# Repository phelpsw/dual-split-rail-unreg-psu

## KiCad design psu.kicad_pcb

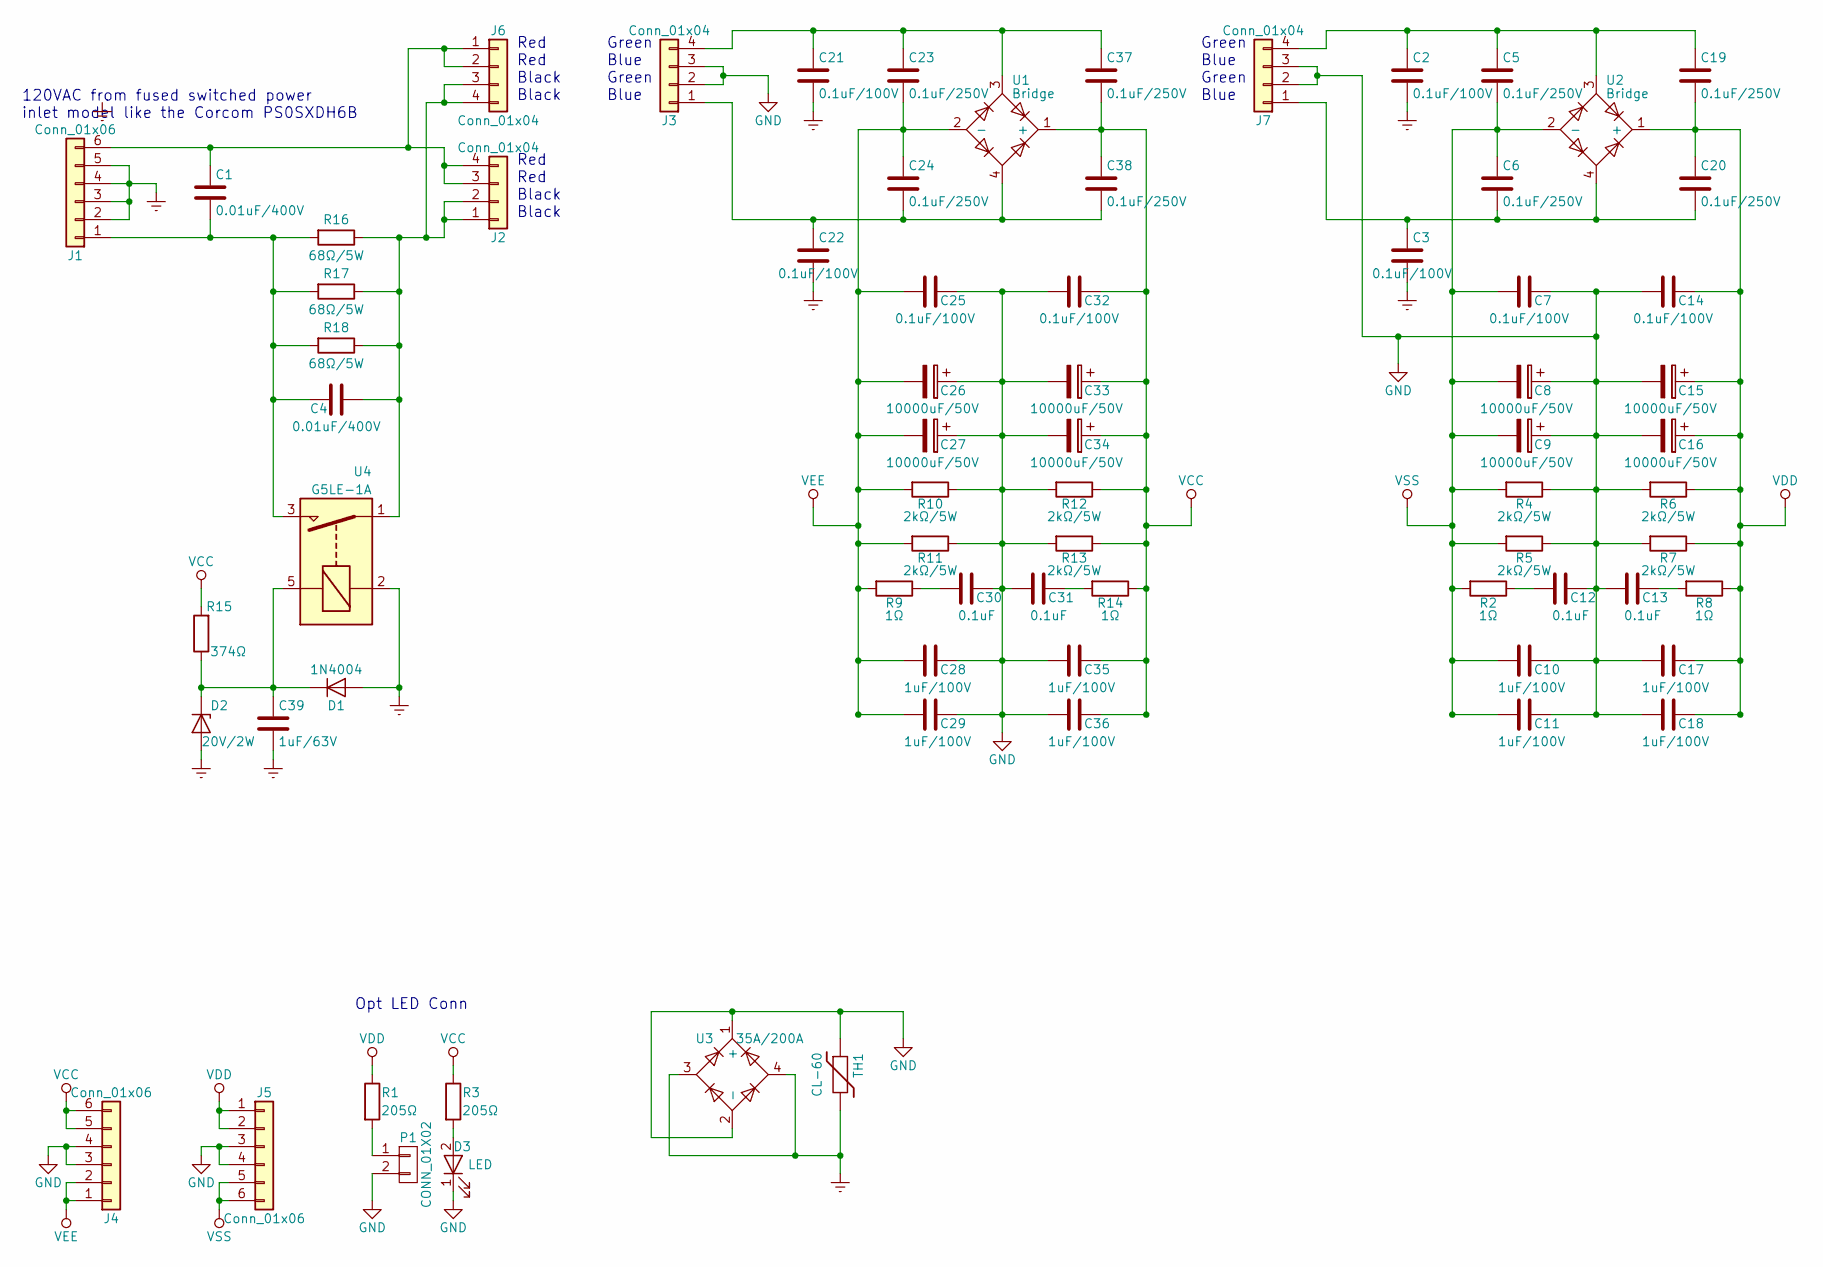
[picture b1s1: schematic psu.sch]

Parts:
C1, C4: 0.01uF/400V; C_Rect_L13.0mm_W4.0mm_P10.00mm_FKS3_FKP3_MKS4
C2, C3, C7, C14, C21, C22, C25, C32: 0.1uF/100V; C_Rect_L7.0mm_W3.5mm_P5.00mm
C5, C6, C19, C20, C23, C24, C37, C38: 0.1uF/250V; C_Rect_L10.3mm_W7.2mm_P7.50mm_MKS4
C8, C9, C15, C16, C26, C27, C33, C34: 10000uF/50V; CP_Radial_D35.0mm_P10.00mm_SnapIn
C10, C11, C17, C18, C28, C29, C35, C36: 1uF/100V; C_Rect_L13.0mm_W6.0mm_P10.00mm_FKS3_FKP3_MKS4
C12, C13, C30, C31: 0.1uF; C_Rect_L7.0mm_W3.5mm_P5.00mm
C39: 1uF/63V; CP_Radial_D5.0mm_P2.00mm
D1: 1N4004; D_DO-41_SOD81_P10.16mm_Horizontal
D2: 20V/2W; D_DO-41_SOD81_P10.16mm_Horizontal
D3: LED; LED_D5.0mm
J1, J4, J5: Conn_01x06; Phoenix-MKDS-6
J2, J3, J6, J7: Conn_01x04; Phoenix-MKDS-4
P1: CONN_01X02; JST_XH_B02B-XH-A_02x2.50mm_Straight
R1, R3: 205Ω; R_Axial_DIN0207_L6.3mm_D2.5mm_P10.16mm_Horizontal
R2, R8, R9, R14: 1Ω; R_Axial_DIN0207_L6.3mm_D2.5mm_P10.16mm_Horizontal
R4, R5, R6, R7, R10, R11, R12, R13: 2kΩ/5W; R_Axial_Power_L25.0mm_W9.0mm_P30.48mm
R15: 374Ω; R_Axial_DIN0309_L9.0mm_D3.2mm_P15.24mm_Horizontal
R16, R17, R18: 68Ω/5W; R_Axial_Power_L25.0mm_W9.0mm_P30.48mm
TH1: CL-60; RV_Disc_D21.5_W5.8_P10
U1, U2: Bridge; GBPC-W
U3: 35A/200A; Diode_Bridge_18.5x5.5
U4: G5LE-1A; Relay_Omron_G5LE-1A4

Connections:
Earth: C2.2, C3.2, C21.2, C22.2, C39.2, D1.2 (A), D2.2 (A), J1.2, J1.3, J1.4, J1.5, TH1.2, U3.3, U3.4, U4.2
GND: C7.1, C8.1, C9.1, C10.1, C11.1, C12.1, C13.2, C14.2, C15.2, C16.2, C17.2, C18.2, C25.1, C26.1, C27.1, C28.1, C29.1, C30.1, C31.2, C32.2, C33.2, C34.2, C35.2, C36.2, D3.1 (K), J3.2, J3.3, J4.3, J4.4, J5.3, J5.4, J7.2, J7.3, P1.2, R4.1, R5.1, R6.2, R7.2, R10.1, R11.1, R12.2, R13.2, TH1.1, U3.1 (+), U3.2 (-)
unnamed: C1.1, J1.6, J2.3, J2.4, J6.1, J6.2
unnamed: C1.2, C4.2, J1.1, R16.2, R17.2, R18.2, U4.3
unnamed: C4.1, J2.1, J2.2, J6.3, J6.4, R16.1, R17.1, R18.1, U4.1
unnamed: C12.2, R2.1
unnamed: C13.1, R8.2
unnamed: C2.1, C5.1, C19.1, J7.4, U2.3
unnamed: C3.1, C6.2, C20.2, J7.1, U2.4
unnamed: C21.1, C23.1, C37.1, J3.4, U1.3
unnamed: C22.1, C24.2, C38.2, J3.1, U1.4
unnamed: C30.2, R9.1
unnamed: C31.1, R14.2
unnamed: C39.1, D1.1 (K), D2.1 (K), R15.1, U4.5
unnamed: D3.2 (A), R3.2
unnamed: P1.1, R1.2
VCC: C32.1, C33.1, C34.1, C35.1, C36.1, C37.2, C38.1, J4.5, J4.6, R3.1, R12.1, R13.1, R14.1, R15.2, U1.1 (+)
VDD: C14.1, C15.1, C16.1, C17.1, C18.1, C19.2, C20.1, J5.1, J5.2, R1.1, R6.1, R7.1, R8.1, U2.1 (+)
VEE: C23.2, C24.1, C25.2, C26.2, C27.2, C28.2, C29.2, J4.1, J4.2, R9.2, R10.2, R11.2, U1.2 (-)
VSS: C5.2, C6.1, C7.2, C8.2, C9.2, C10.2, C11.2, J5.5, J5.6, R2.2, R4.2, R5.2, U2.2 (-)

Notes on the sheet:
Red Red Black Black
Green Blue Green Blue
Opt LED Conn
120VAC from fused switched power inlet model like the Corcom PS0SXDH6B

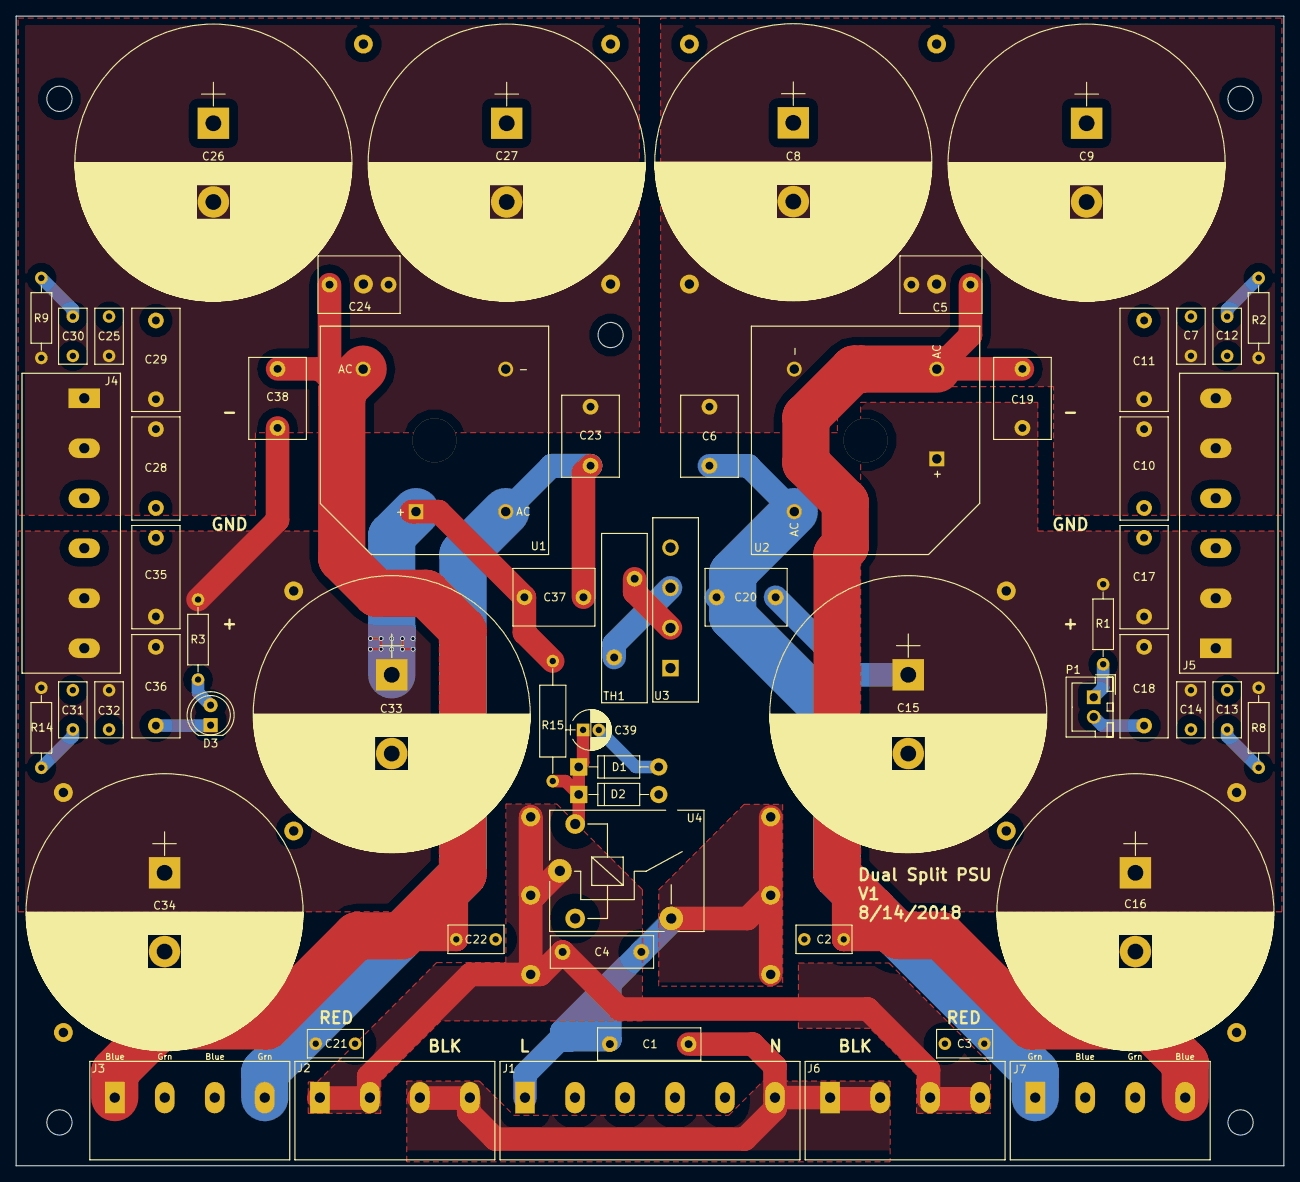
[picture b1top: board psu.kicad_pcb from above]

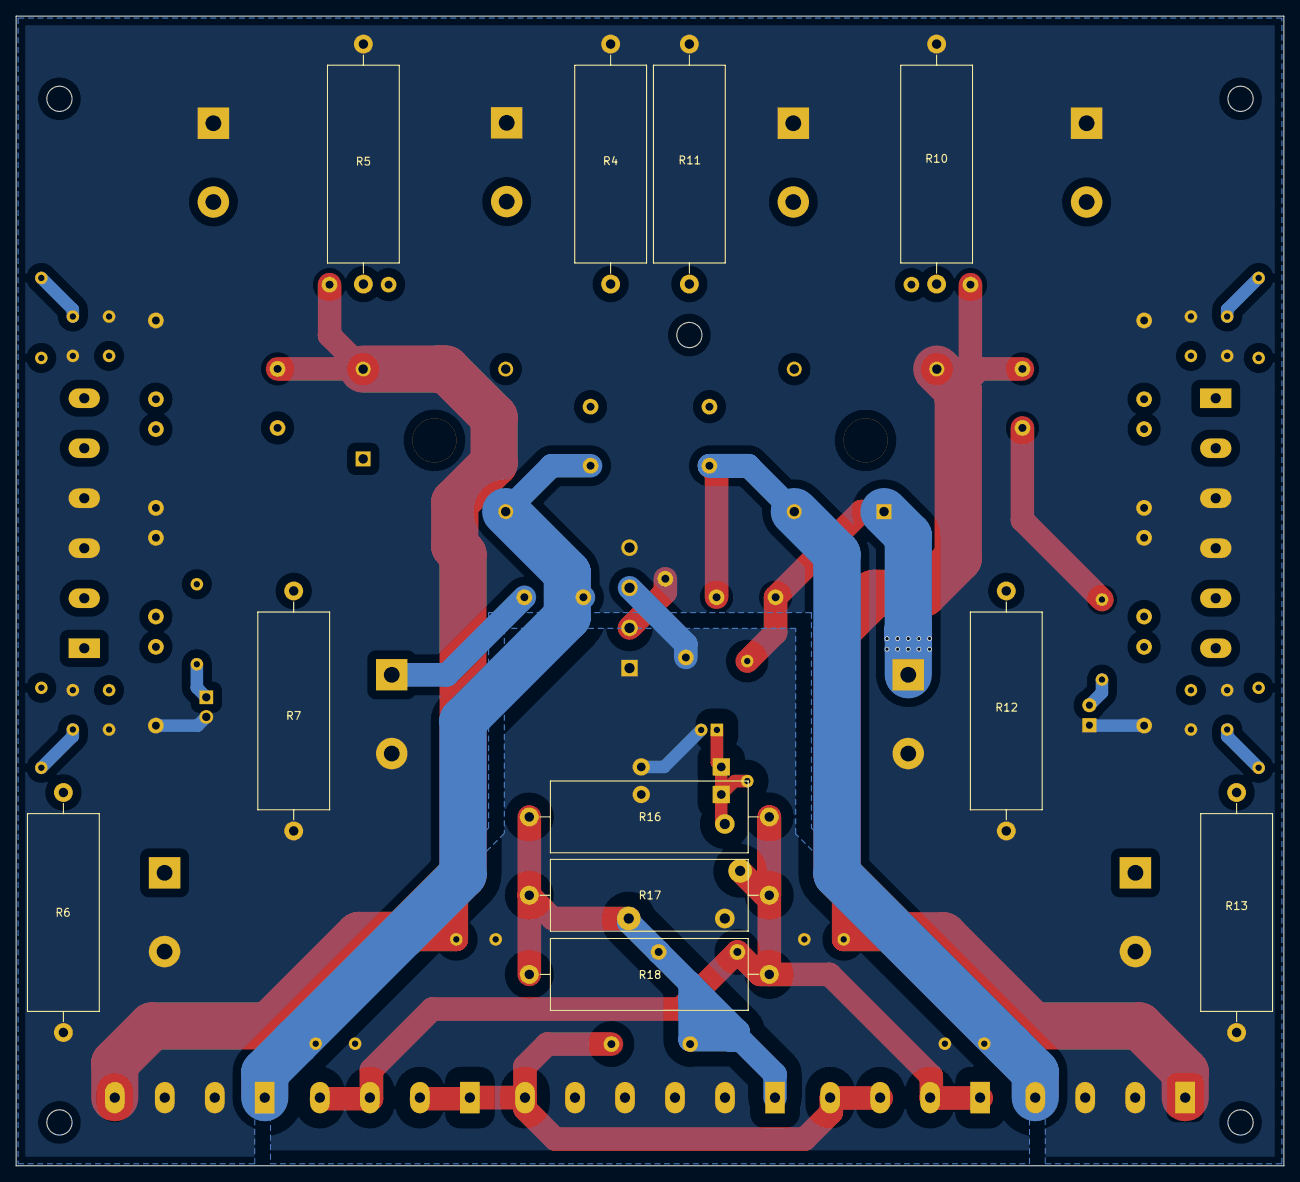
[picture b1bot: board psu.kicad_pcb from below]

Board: 2 copper layers, 161.0 x 146.0 mm, 73 parts (11 on the bottom side), 20 nets.

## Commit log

2018-08-25 schematic pdf
2018-09-17 Adding some psu project files
